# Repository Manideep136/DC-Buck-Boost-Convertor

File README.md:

# DC Buck-Boost Converter – KiCad PCB Design

## 📌 Project Overview

This project focuses on the design of a **DC-DC Buck-Boost Converter PCB** using KiCad. A buck-boost converter is a switching power converter that can regulate a DC output voltage that may be either higher or lower than the input voltage, depending on the converter topology and operating conditions.

The project covers schematic design, component selection, footprint assignment, PCB layout, copper routing, and design verification.

## 🎯 Project Objectives

- Design a DC-DC buck-boost converter circuit.
- Create the schematic using KiCad.
- Select suitable components and footprints.
- Design a compact and organized PCB layout.
- Route power and signal connections.
- Implement appropriate grounding and power routing.
- Perform Electrical Rules Check (ERC) and Design Rules Check (DRC).
- Prepare the design for potential PCB fabrication.

## ⚙️ Working Principle

A buck-boost converter uses switching components, energy-storage elements, and control circuitry to regulate its output voltage.

1. **DC Input:** The circuit receives power from a DC source.
2. **Switching Operation:** The converter IC controls switching to transfer energy through the power stage.
3. **Energy Storage:** An inductor stores and releases energy during switching cycles.
4. **Voltage Regulation:** Capacitors filter the input and output voltage, while the control circuit regulates the output.
5. **DC Output:** The circuit provides a regulated DC voltage suitable for the intended application.

### Block Diagram

```text
       DC Input Supply
              │
              ▼
     Buck-Boost Converter
        Switching Stage
              │
       ┌──────┴──────┐
       │             │
    Inductor     Capacitors
       │             │
       └──────┬──────┘
              │
              ▼
       Regulated DC Output
```

*The exact circuit operation depends on whether the selected IC uses an inverting, non-inverting, synchronous, or asynchronous buck-boost topology.*

## 🔧 Main Components

| Component               | Function                                                      |
| ----------------------- | ------------------------------------------------------------- |
| Buck-boost converter IC | Controls voltage conversion                                   |
| Inductor                | Stores and transfers energy                                   |
| Input capacitors        | Reduce input voltage fluctuations                             |
| Output capacitors       | Filter output ripple                                          |
| Feedback resistors      | Set the regulated output voltage when required                |
| Diodes or MOSFETs       | Switching and energy-transfer elements, depending on topology |
| Input connector         | Connects the DC power source                                  |
| Output connector        | Provides the regulated output                                 |
| PCB                     | Supports and interconnects the circuit components             |

*Refer to the actual schematic and the selected IC's datasheet for the final component values and ratings.*

## 🖥️ Software and Tools

- **KiCad** – Electronic schematic and PCB design
- KiCad Schematic Editor
- KiCad PCB Editor
- Symbol and footprint libraries
- KiCad 3D Viewer
- Electrical Rules Check (ERC)
- Design Rules Check (DRC)

## 🧩 PCB Design Workflow

### 1. Schematic Design

The converter circuit was created in KiCad, including the controller IC, switching stage, inductor, capacitors, feedback network, and input/output connections as required by the selected design.

### 2. Component and Footprint Selection

Appropriate symbols and footprints were assigned according to the component datasheets. Package dimensions and pin numbering should be verified before routing.

### 3. Component Placement

Components were arranged to keep high-current paths short, place decoupling capacitors close to the relevant IC pins, and separate sensitive feedback signals from noisy switching nodes.

### 4. PCB Routing

Copper tracks were routed according to the schematic and the expected current requirements. Wider traces may be needed in high-current paths.

### 5. Grounding and Copper Zones

GND copper zones can provide low-impedance return paths when used appropriately. The ground layout should follow the converter IC manufacturer's recommended PCB layout.

### 6. Design Verification

ERC and DRC are used to check electrical connections, clearance violations, track widths, board-edge spacing, and other design issues.

### 7. Manufacturing Preparation

After final verification, Gerber files, drill files, and the bill of materials (BOM) can be prepared for fabrication and assembly.

## 📐 PCB Design Considerations

- Follow the converter IC manufacturer's recommended layout.
- Place input bypass capacitors close to the power input pins.
- Minimize the area of high-frequency switching-current loops.
- Keep switching nodes away from sensitive feedback signals.
- Select an inductor with suitable inductance, saturation current, and thermal rating.
- Verify capacitor voltage ratings and ripple-current capability.
- Choose suitable trace widths for the intended current.
- Provide adequate copper area for heat dissipation where necessary.
- Check input polarity and output connections.
- Verify all footprints and pin assignments before manufacturing.

## 🔍 Design Verification Checklist

- [x] Schematic completed
- [x] Component values verified
- [x] Footprints checked against datasheets
- [x] PCB placement completed
- [x] Copper routing completed
- [x] ERC completed
- [x] DRC completed
- [x] Grounding and switching loops reviewed
- [x] Thermal considerations reviewed
- [x] Silkscreen and board outline checked
- [x] Gerber and drill files generated

## 📂 Repository Structure

```text
DC-Buck-Boost-Converter/
│
├── README.md
├── Schematic/
│   └── Buck_Boost_Converter.kicad_sch
├── PCB/
│   └── Buck_Boost_Converter.kicad_pcb
├── Images/
│   ├── schematic.png
│   ├── pcb-layout.png
│   └── 3d-view.png
├── BOM/
│   └── BOM.csv
└── Gerber/
    └── Manufacturing_Files/
```

## 🚧 Project Status

| Stage                | Status                            |
| -------------------- | --------------------------------- |
| Schematic design     | Update to reflect actual progress |
| Footprint assignment | Update to reflect actual progress |
| PCB layout           | Update to reflect actual progress |
| Routing              | Update to reflect actual progress |
| ERC/DRC verification | Pending final confirmation        |
| Manufacturing files  | Optional                          |
| PCB fabrication      | Not claimed                       |
| Hardware testing     | Not claimed                       |

## 🚀 Future Improvements

- Optimize the PCB for improved efficiency and reduced switching noise.
- Improve thermal performance.
- Add input reverse-polarity protection where appropriate.
- Add overcurrent or short-circuit protection if supported by the design.
- Add clearly labeled input and output test points.
- Fabricate and test the PCB under controlled conditions.
- Document measured output voltage, load regulation, efficiency, and ripple after testing.

## 📚 Learning Outcomes

This project develops practical skills in:

- Switching power-supply design
- KiCad schematic creation
- Component selection and footprint verification
- PCB placement and copper routing
- Ground-plane design
- Power integrity and thermal considerations
- ERC and DRC verification
- PCB documentation and manufacturing preparation

## ⚠️ Safety and Testing

Use a suitable current-limited DC power supply during testing. Confirm the converter's input range, output range, current limits, component ratings, and thermal limits before connecting a load. Do not assume a particular output voltage or current rating without verifying the completed design.

## 🛠️ Project Information

**Project:** DC Buck-Boost Converter PCB
**Design Software:** KiCad
**Project Type:** Power Electronics / PCB Design
**Deliverables:** Schematic, PCB layout, and optional manufacturing files

---

*This repository documents the PCB design. Manufacturing and hardware testing should only be marked complete after they have actually been performed.*

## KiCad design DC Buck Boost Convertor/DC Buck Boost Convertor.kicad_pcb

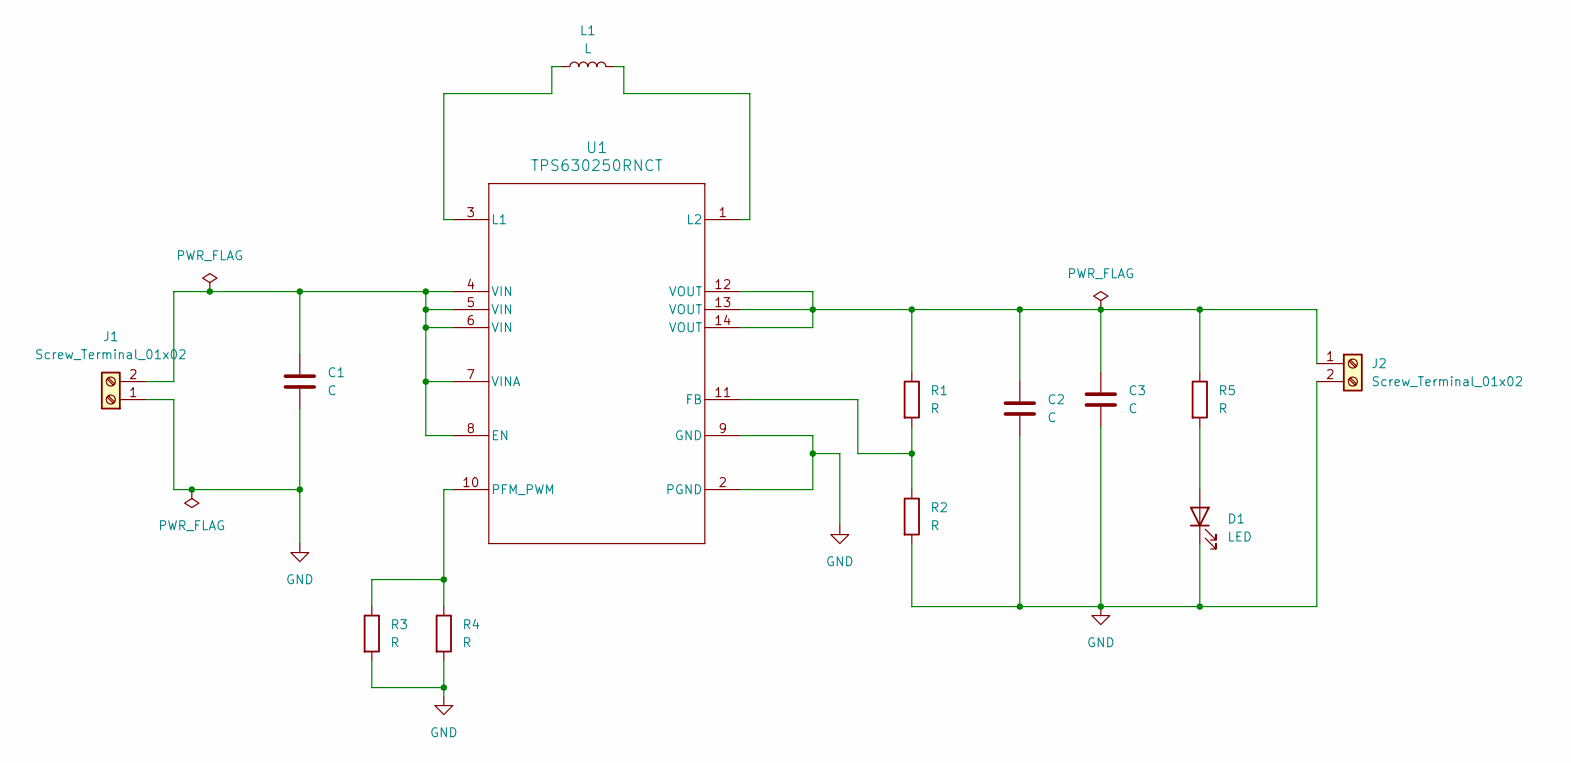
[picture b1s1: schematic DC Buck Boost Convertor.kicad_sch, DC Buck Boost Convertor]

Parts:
C1, C2, C3: C; C_1825_4564Metric
D1: LED; LED_1812_4532Metric
J1, J2: Screw_Terminal_01x02; TerminalBlock_Phoenix_MKDS-1,5-2_1x02_P5.00mm_Horizontal
L1: L; L_2010_5025Metric
R1, R2, R3, R4, R5: R; R_0805_2012Metric
U1: TPS630250RNCT; RNC0014A

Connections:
GND: C1.2, C2.2, C3.2, D1.1 (K), J1.1, J2.2, R2.2, R3.2, R4.2, U1.2 (PGND), U1.9 (GND)
unnamed: D1.2 (A), R5.2
unnamed: C1.1, J1.2, U1.4 (VIN), U1.5 (VIN), U1.6 (VIN), U1.7 (VINA), U1.8 (EN)
unnamed: C2.1, C3.1, J2.1, R1.1, R5.1, U1.12 (VOUT), U1.13 (VOUT), U1.14 (VOUT)
unnamed: R1.2, R2.1, U1.11 (FB)
unnamed: L1.1, U1.3 (L1)
unnamed: L1.2, U1.1 (L2)
unnamed: R3.1, R4.1, U1.10 (PFM_PWM)

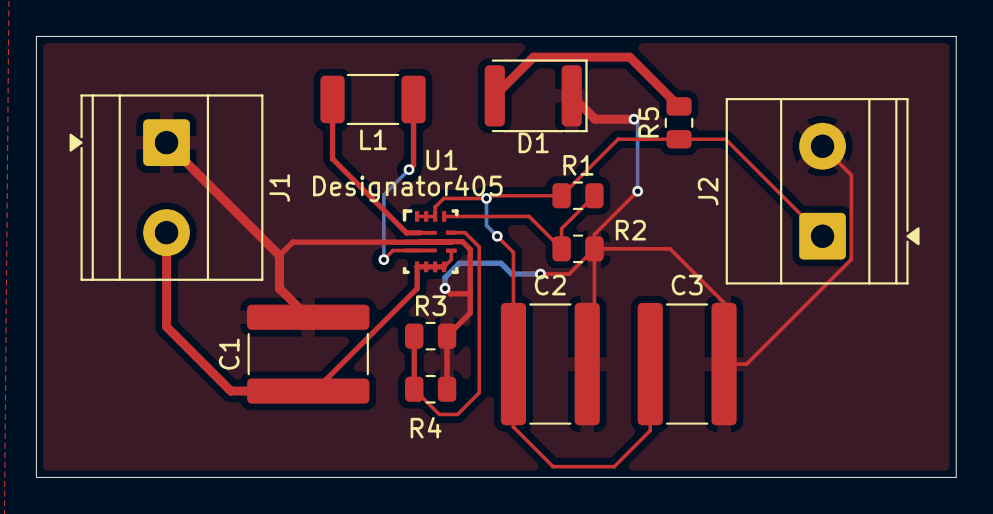
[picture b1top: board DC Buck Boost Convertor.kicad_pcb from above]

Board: 2 copper layers, 51.1 x 24.5 mm, 13 parts (0 on the bottom side), 8 nets.
